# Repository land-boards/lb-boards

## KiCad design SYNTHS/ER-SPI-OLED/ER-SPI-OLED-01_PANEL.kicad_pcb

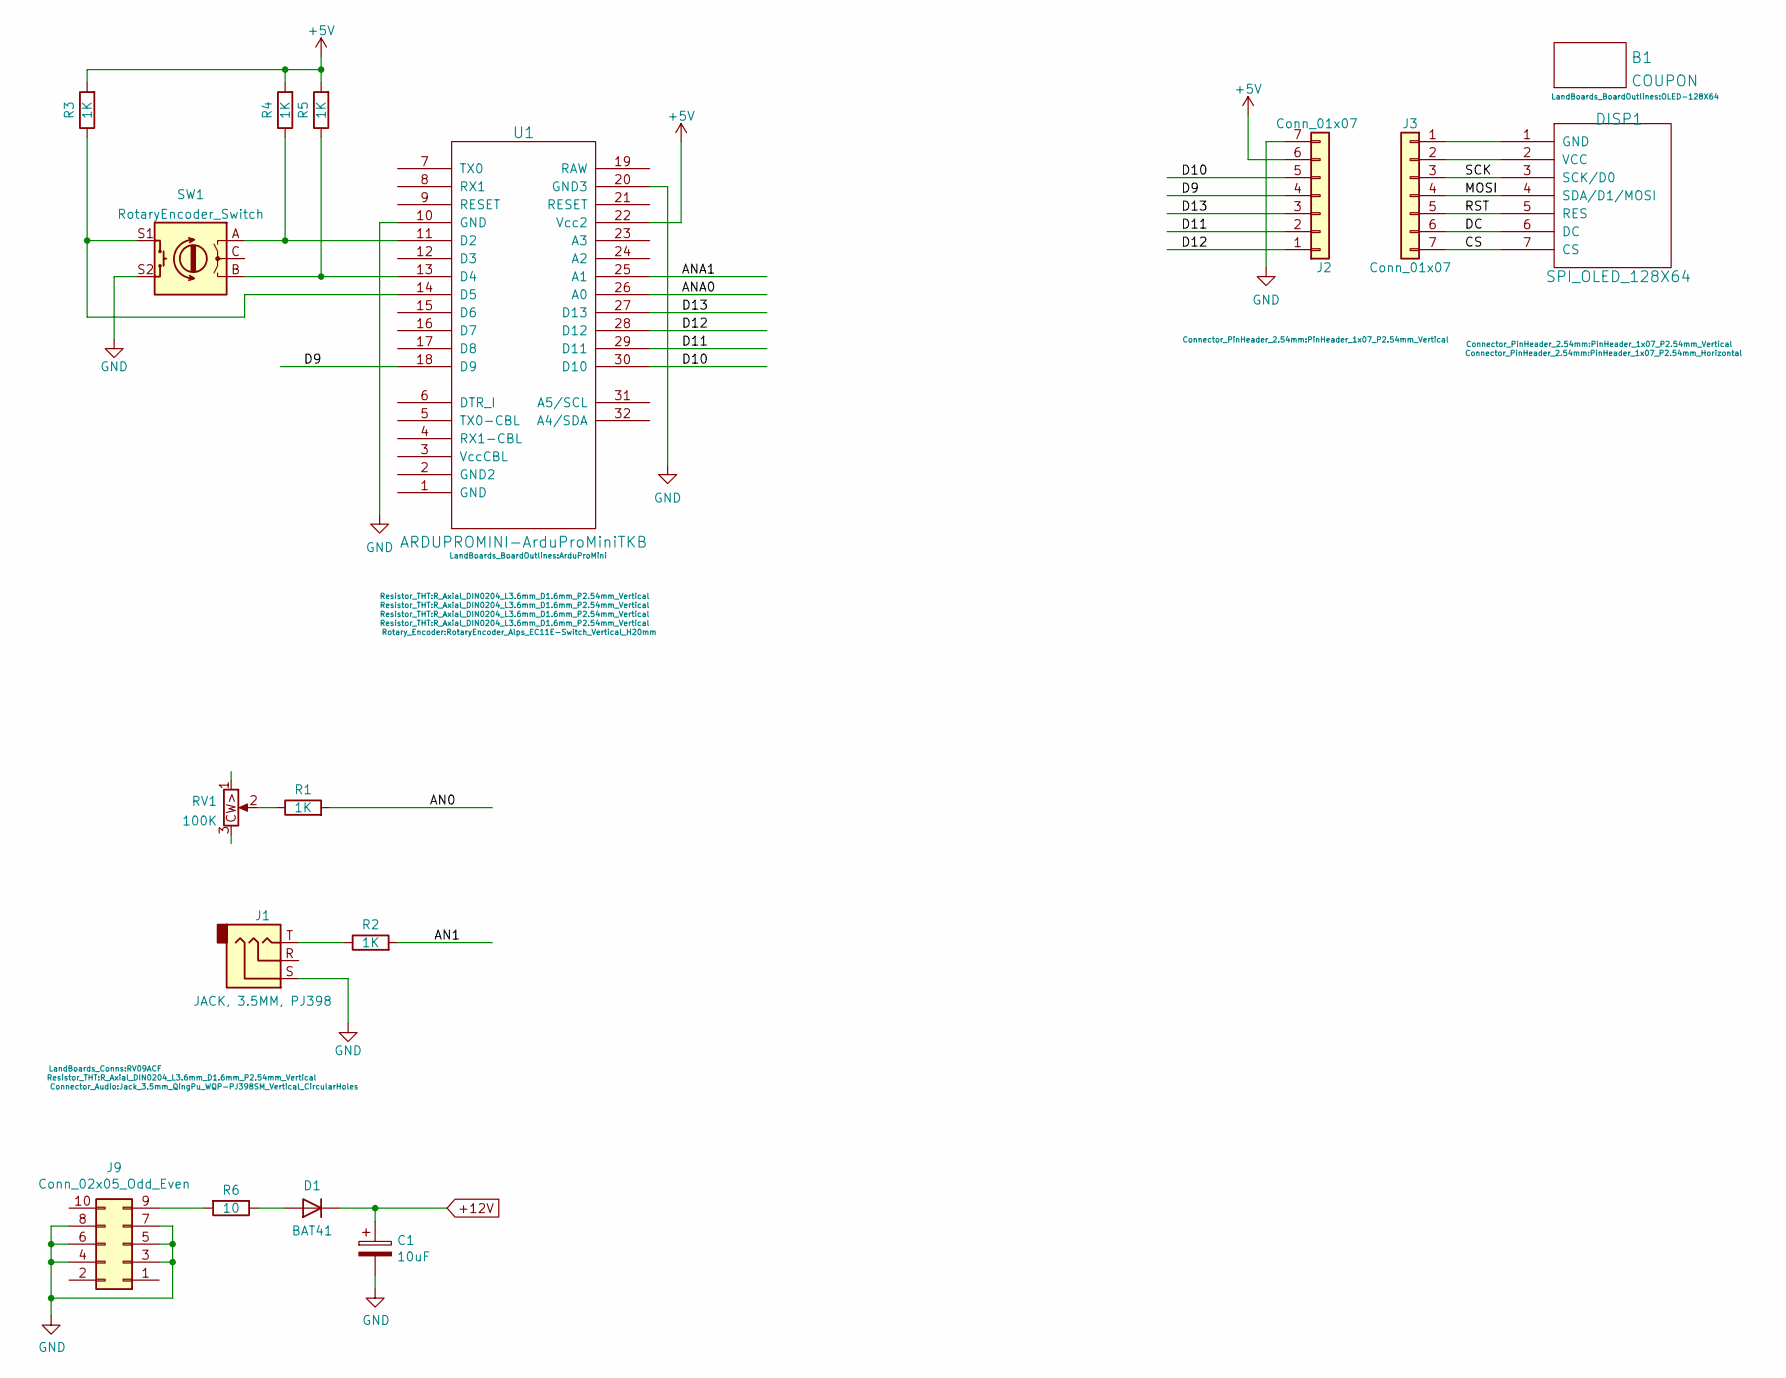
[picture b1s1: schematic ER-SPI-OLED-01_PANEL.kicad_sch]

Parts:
B1: COUPON; OLED-128X64
C1: 10uF; CP_Radial_D6.3mm_P2.50mm
D1: BAT41; D_DO-41_SOD81_P7.62mm_Horizontal
DISP1: SPI_OLED_128X64; PinHeader_1x07_P2.54mm_Vertical
J1: JACK, 3.5MM, PJ398; Jack_3.5mm_QingPu_WQP-PJ398SM_Vertical_CircularHoles
J2: Conn_01x07; PinHeader_1x07_P2.54mm_Vertical
J3: Conn_01x07; PinHeader_1x07_P2.54mm_Horizontal
J9: Conn_02x05_Odd_Even; IDC-Header_2x05_P2.54mm_Vertical
R1, R2, R3, R4, R5: 1K; R_Axial_DIN0204_L3.6mm_D1.6mm_P2.54mm_Vertical
R6: 10; R_Axial_DIN0207_L6.3mm_D2.5mm_P7.62mm_Horizontal
RV1: 100K; RV09ACF
SW1: RotaryEncoder_Switch; RotaryEncoder_Alps_EC11E-Switch_Vertical_H20mm
U1: ARDUPROMINI-ArduProMiniTKB; ArduProMini

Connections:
+5V: J2.6, R3.2, R4.2, R5.2, U1.22 (Vcc2)
+12V: C1.1, D1.1 (K)
/AN0: R1.2
/AN1: R2.2
/ANA0: U1.26 (A0)
/ANA1: U1.25 (A1)
/CS: DISP1.7 (CS), J3.7
/D9: J2.4, U1.18 (D9)
/D10: J2.5, U1.30 (D10)
/D11: J2.2, U1.29 (D11)
/D12: J2.1, U1.28 (D12)
/D13: J2.3, U1.27 (D13)
/DC: DISP1.6 (DC), J3.6
/MOSI: DISP1.4 (SDA/D1/MOSI), J3.4
/RST: DISP1.5 (RES), J3.5
/SCK: DISP1.3 (SCK/D0), J3.3
GND: C1.2, J1.S, J2.7, J9.3, J9.4, J9.5, J9.6, J9.7, J9.8, SW1.S2, U1.10 (GND), U1.20 (GND3)
unnamed: D1.2 (A), R6.1
unnamed: DISP1.1 (GND), J3.1
unnamed: DISP1.2 (VCC), J3.2
unnamed: J1.T, R2.1
unnamed: J9.9, R6.2
unnamed: R1.1, RV1.2
unnamed: R3.1, SW1.S1, U1.14 (D5)
unnamed: R4.1, SW1.A, U1.11 (D2)
unnamed: R5.1, SW1.B, U1.13 (D4)

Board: 2 copper layers, 17 parts (2 on the bottom side), 22 nets, no tracks yet.

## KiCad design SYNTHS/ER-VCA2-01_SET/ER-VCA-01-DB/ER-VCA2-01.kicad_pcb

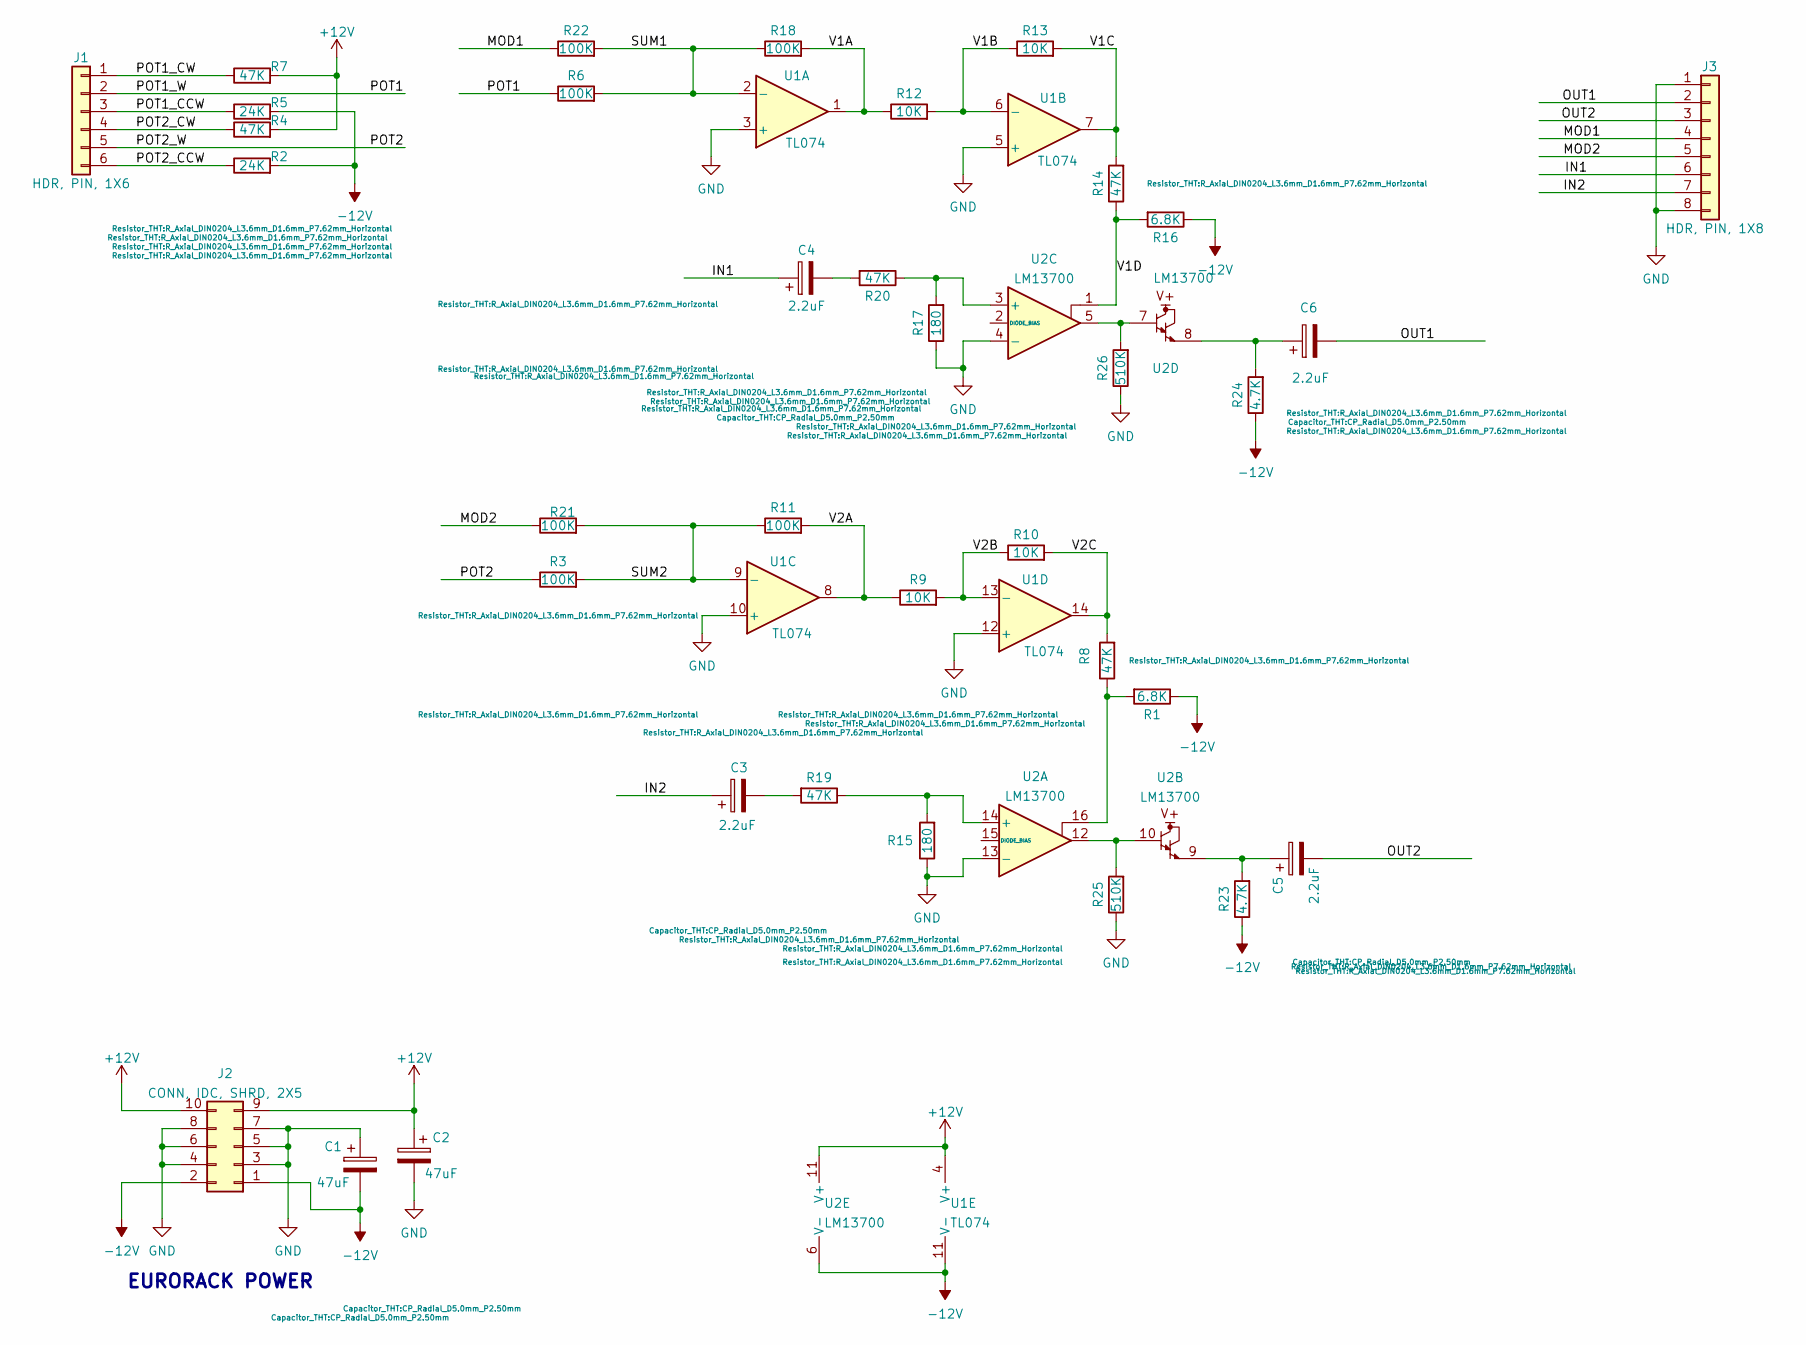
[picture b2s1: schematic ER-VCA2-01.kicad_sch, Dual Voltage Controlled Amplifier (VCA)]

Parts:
C1, C2: 47uF; CP_Radial_D5.0mm_P2.50mm
C3, C4, C5, C6: 2.2uF; CP_Radial_D5.0mm_P2.50mm
J1: HDR, PIN, 1X6; PinSocket_1x06_P2.54mm_Vertical
J2: CONN, IDC, SHRD, 2X5; IDC-Header_2x05_P2.54mm_Vertical
J3: HDR, PIN, 1X8; PinSocket_1x08_P2.54mm_Vertical
R1, R16: 6.8K; R_Axial_DIN0204_L3.6mm_D1.6mm_P7.62mm_Horizontal
R2, R5: 24K; R_Axial_DIN0204_L3.6mm_D1.6mm_P7.62mm_Horizontal
R3, R6, R11, R18, R21, R22: 100K; R_Axial_DIN0204_L3.6mm_D1.6mm_P7.62mm_Horizontal
R4, R7, R8, R14, R19, R20: 47K; R_Axial_DIN0204_L3.6mm_D1.6mm_P7.62mm_Horizontal
R9, R10, R12, R13: 10K; R_Axial_DIN0204_L3.6mm_D1.6mm_P7.62mm_Horizontal
R15, R17: 180; R_Axial_DIN0204_L3.6mm_D1.6mm_P7.62mm_Horizontal
R23, R24: 4.7K; R_Axial_DIN0204_L3.6mm_D1.6mm_P7.62mm_Horizontal
R25, R26: 510K; R_Axial_DIN0204_L3.6mm_D1.6mm_P7.62mm_Horizontal
U1: TL074
U2: LM13700

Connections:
+12V: C2.1, J2.9, J2.10, R4.2, R7.2, U1.4 (V+), U2.11 (V+)
-12V: C1.2, J2.1, J2.2, R1.1, R2.2, R5.2, R16.1, R23.1, R24.1, U1.11 (V-), U2.6 (V-)
/IN1: C4.1, J3.6
/IN2: C3.1, J3.7
/MOD1: J3.4, R22.1
/MOD2: J3.5, R21.1
/OUT1: C6.2, J3.2
/OUT2: C5.2, J3.3
/POT1: J1.2, R6.1
/POT1_CCW: J1.3, R5.1
/POT1_CW: J1.1, R7.1
/POT2: J1.5, R3.1
/POT2_CCW: J1.6, R2.1
/POT2_CW: J1.4, R4.1
/SUM1: R6.2, R18.1, R22.2, U1.2 (-)
/SUM2: R3.2, R11.1, R21.2, U1.9 (-)
/V1A: R12.1, R18.2, U1.1
/V1B: R12.2, R13.1, U1.6 (-)
/V1C: R13.2, R14.2, U1.7
/V1D: R14.1, R16.2, U2.1
/V2A: R9.1, R11.2, U1.8
/V2B: R9.2, R10.1, U1.13 (-)
/V2C: R8.2, R10.2, U1.14
GND: C1.1, C2.2, J2.3, J2.4, J2.5, J2.6, J2.7, J2.8, J3.1, J3.8, R15.1, R17.1, R25.1, R26.1, U1.3 (+), U1.5 (+), U1.10 (+), U1.12 (+), U2.4 (-), U2.13 (-)
unnamed: C3.2, R19.2
unnamed: C4.2, R20.2
unnamed: C5.1, R23.2, U2.9
unnamed: C6.1, R24.2, U2.8
unnamed: R1.2, R8.1, U2.16
unnamed: R15.2, R19.1, U2.14 (+)
unnamed: R17.2, R20.1, U2.3 (+)
unnamed: R25.2, U2.10, U2.12
unnamed: R26.2, U2.5, U2.7

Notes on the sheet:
EURORACK POWER

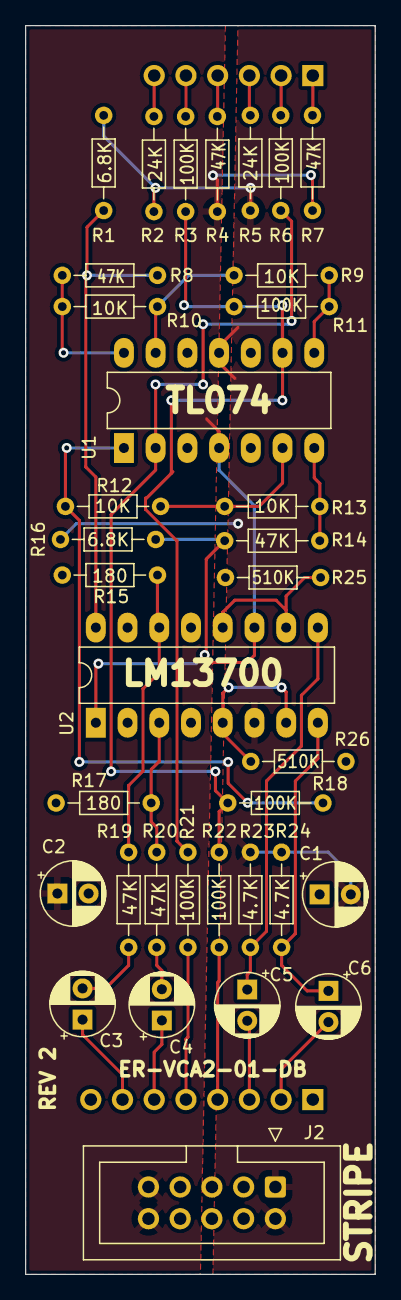
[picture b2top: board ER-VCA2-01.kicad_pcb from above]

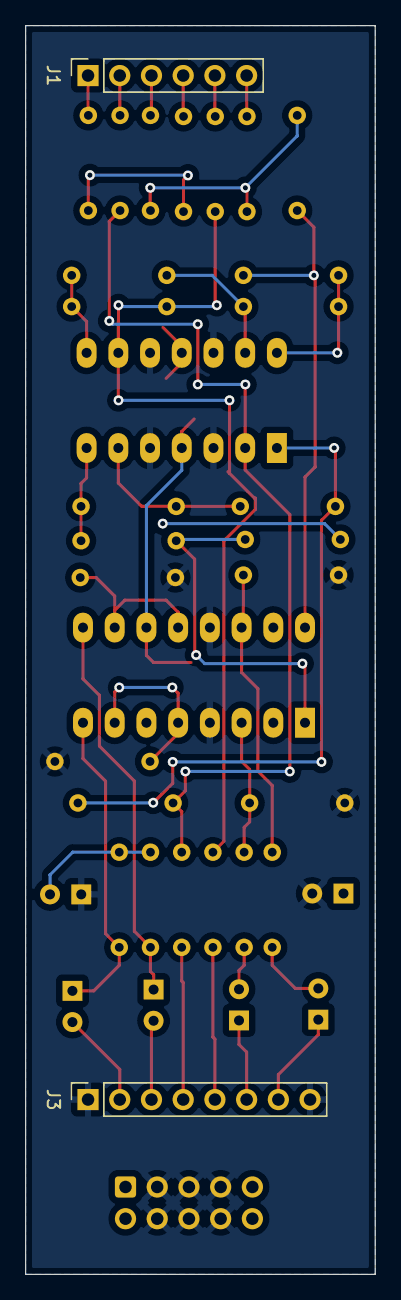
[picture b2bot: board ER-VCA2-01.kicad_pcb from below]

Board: 2 copper layers, 28.0 x 100.0 mm, 37 parts (2 on the bottom side), 33 nets.

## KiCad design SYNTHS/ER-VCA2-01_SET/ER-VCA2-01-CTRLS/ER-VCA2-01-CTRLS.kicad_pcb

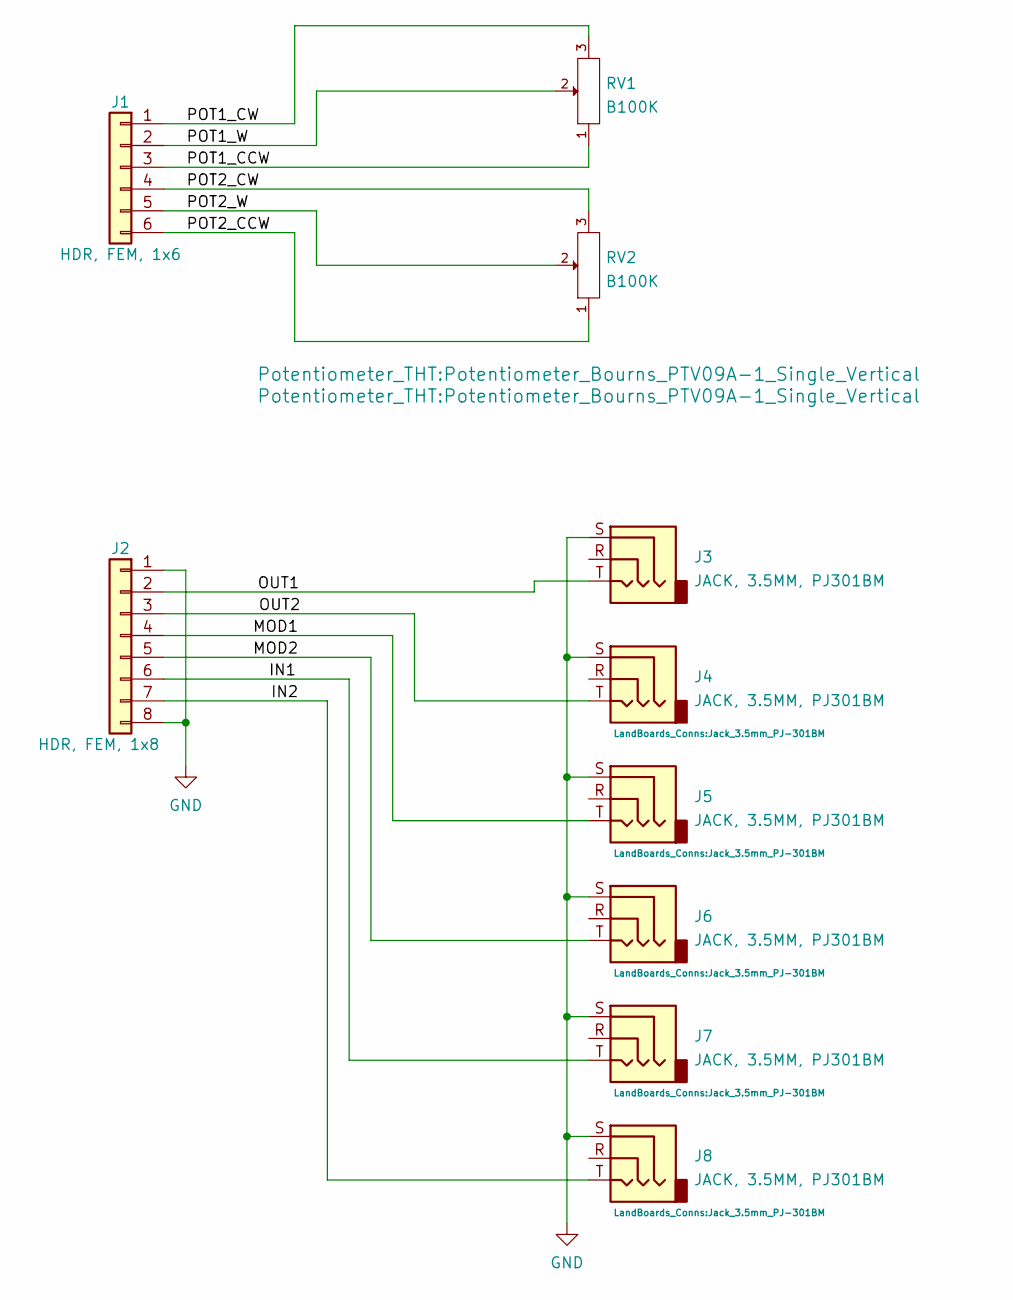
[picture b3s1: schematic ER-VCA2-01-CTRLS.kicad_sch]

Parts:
J1: HDR, FEM, 1x6; PinSocket_1x06_P2.54mm_Vertical
J2: HDR, FEM, 1x8; PinSocket_1x08_P2.54mm_Vertical
J3, J4, J5, J6, J7, J8: JACK, 3.5MM, PJ301BM; Jack_3.5mm_PJ-301BM
RV1, RV2: B100K; Potentiometer_Bourns_PTV09A-1_Single_Vertical

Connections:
/IN1: J2.6, J7.T
/IN2: J2.7, J8.T
/MOD1: J2.4, J5.T
/MOD2: J2.5, J6.T
/OUT1: J2.2, J3.T
/OUT2: J2.3, J4.T
/POT1_CCW: J1.3, RV1.1
/POT1_CW: J1.1, RV1.3
/POT1_W: J1.2, RV1.2
/POT2_CCW: J1.6, RV2.1
/POT2_CW: J1.4, RV2.3
/POT2_W: J1.5, RV2.2
GND: J2.1, J2.8, J3.S, J4.S, J5.S, J6.S, J7.S, J8.S

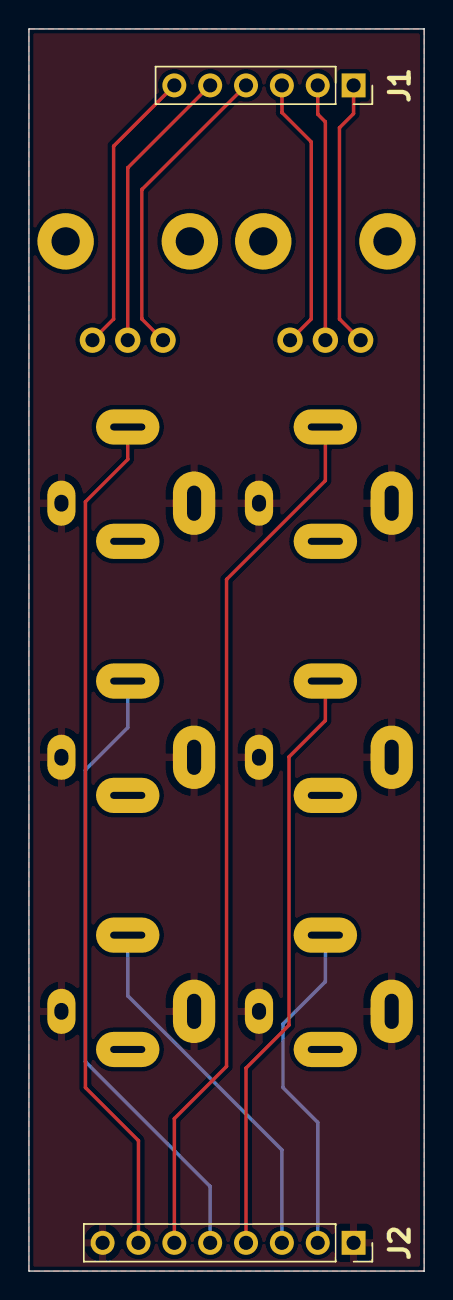
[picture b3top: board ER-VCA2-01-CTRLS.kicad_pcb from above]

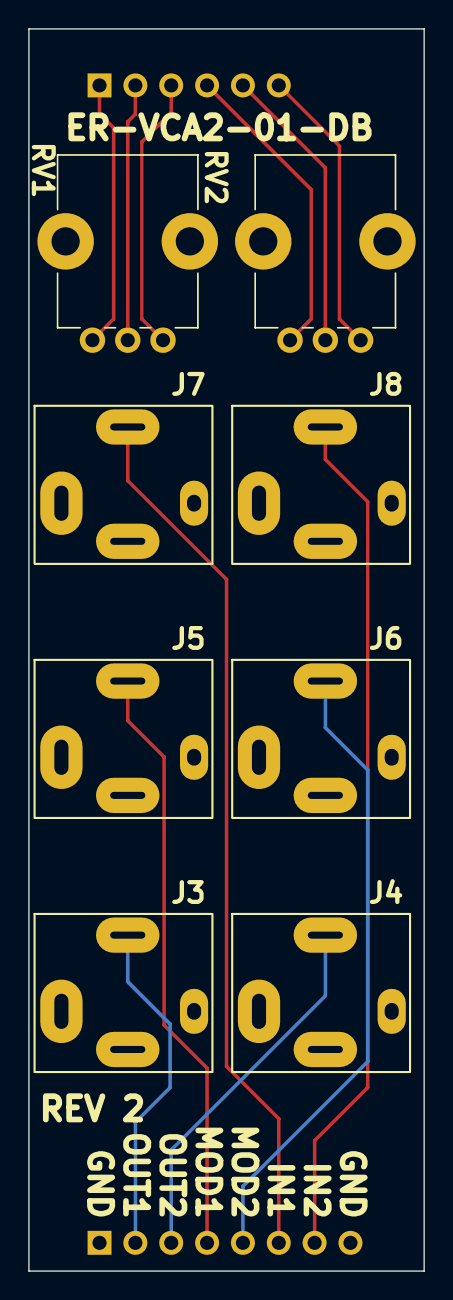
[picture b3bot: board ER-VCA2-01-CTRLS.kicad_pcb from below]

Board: 2 copper layers, 28.0 x 88.0 mm, 10 parts (8 on the bottom side), 13 nets.
